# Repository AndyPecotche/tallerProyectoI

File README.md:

# Pasos 
1. Teniendo un workspace funcioal en eclipse, apuntando a un firmware_v3 ya funcionando, dirigirse a la carpeta donde se encuentra el mismo en el sistema.
1. Una vez en el directorio donde se encuentra el proyecto con un nombre como "firmware_v3-r1.3.0" o "firmware_v3" o "firmware_v3-master", eliminar o mover o renombrar esa carpeta a otro lado.
1. Clonar este repositorio
1. Renombrar el directorio del repositorio clonado con el mismo nombre del directorio del paso anterior (es importante que sea exactamente el mismo).
1. Al abrir eclipse en el workspace que se venia trabajando se deberia reconocer el nuevo proyecto con algunos cambios, pero aun funcionando los comandos de build y deploy.

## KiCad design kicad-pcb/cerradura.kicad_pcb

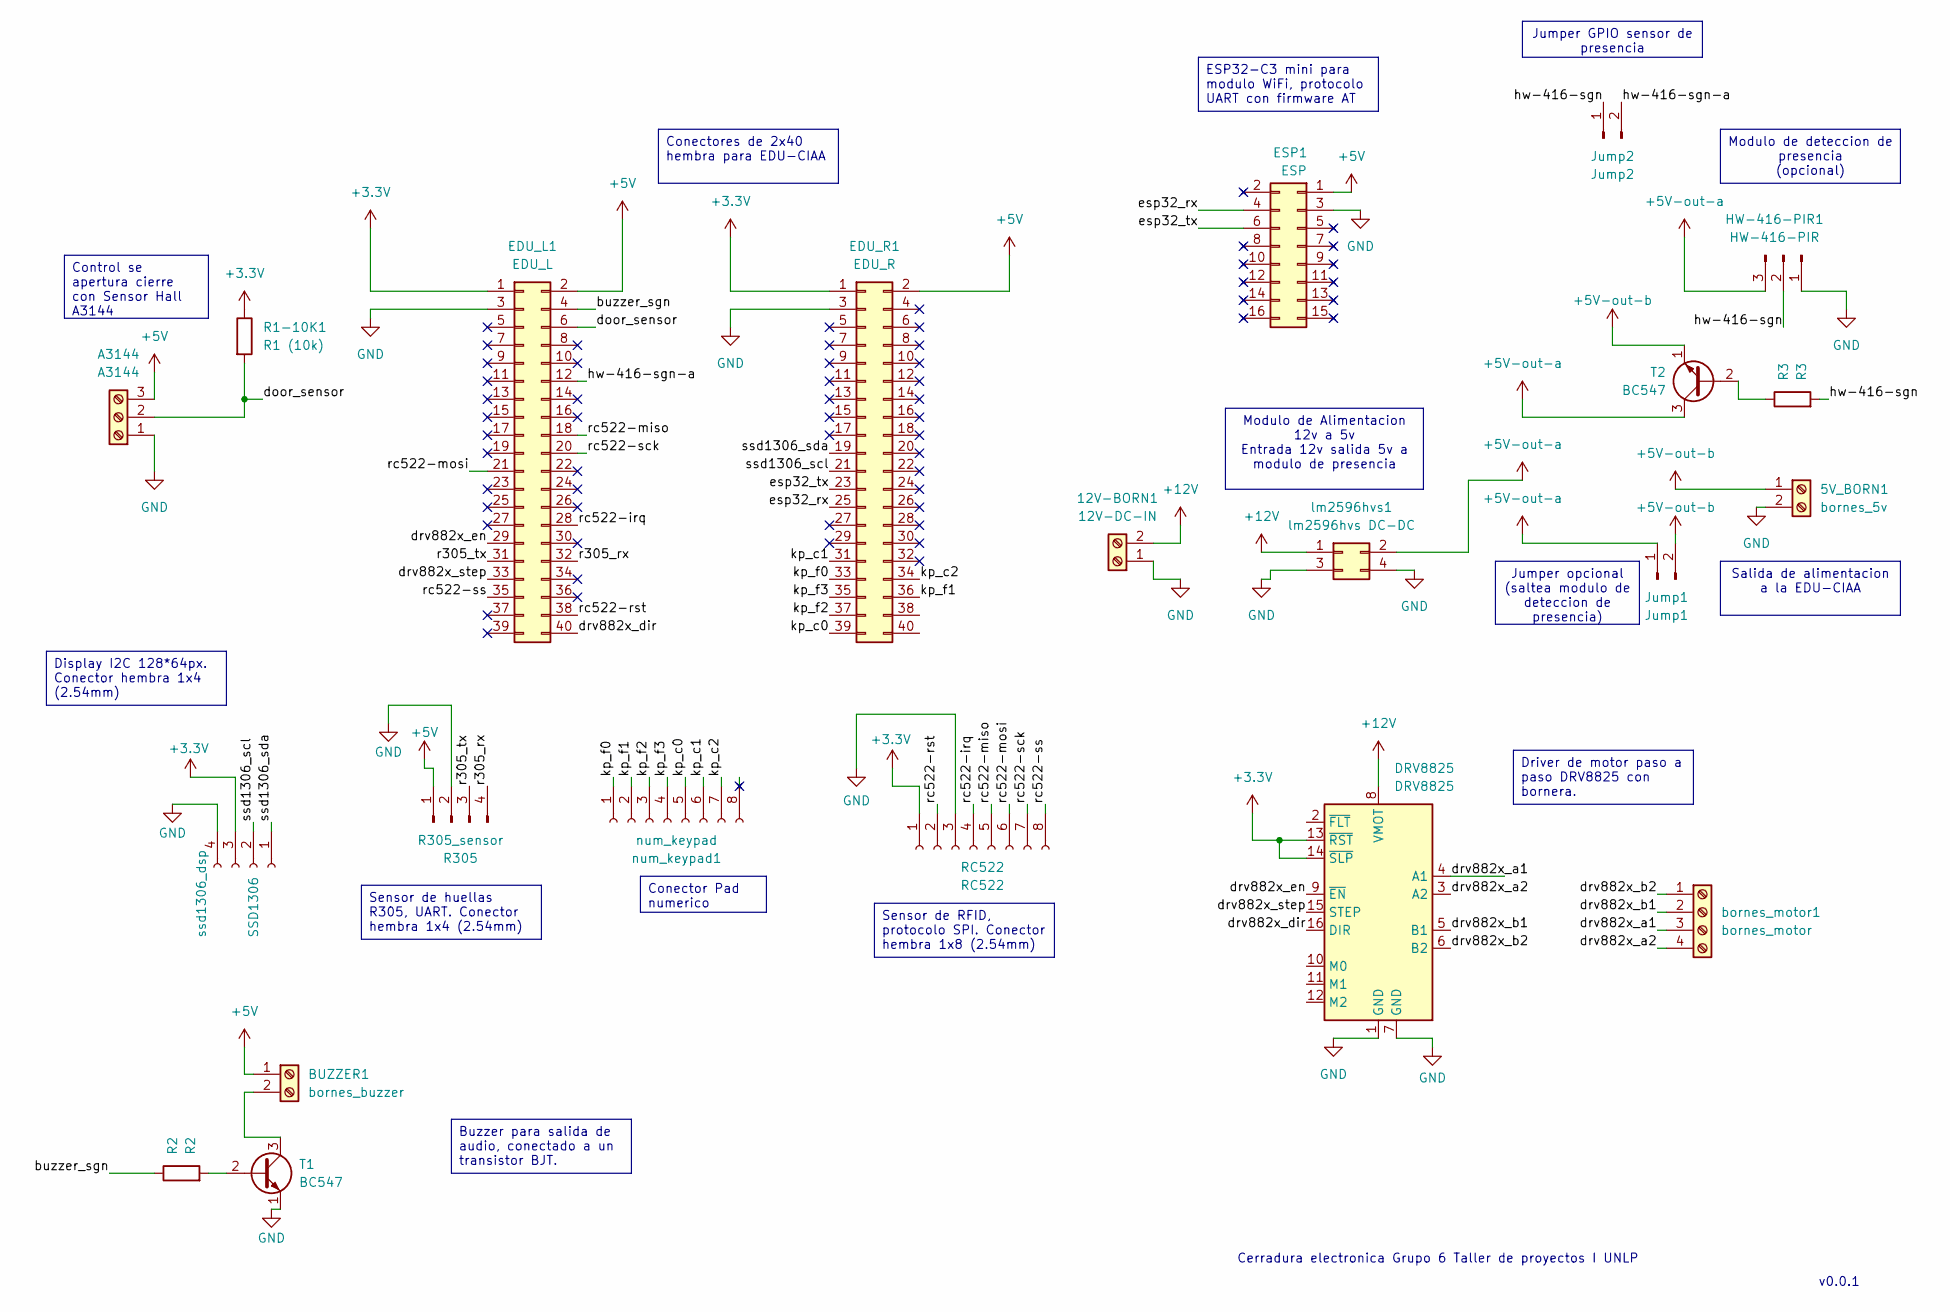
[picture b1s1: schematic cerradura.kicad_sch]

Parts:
5V_BORN1: bornes_5v; TerminalBlock_Altech_AK300-2_P5.00mm
12V-BORN1: 12V-DC-IN; TerminalBlock_Altech_AK300-2_P5.00mm
A3144: A3144; TerminalBlock_Altech_AK300-3_P5.00mm
BUZZER1: bornes_buzzer; TerminalBlock_Altech_AK300-2_P5.00mm
DRV8825: DRV8825; Pololu_Breakout-16_15.2x20.3mm
EDU_L1: EDU_L; IDC-Header_2x20_P2.54mm_Vertical
EDU_R1: EDU_R; IDC-Header_2x20_P2.54mm_Vertical
ESP1: ESP; PinSocket_2x08_P2.54mm_Vertical
HW-416-PIR1: HW-416-PIR; PinSocket_1x03_P2.54mm_Vertical
Jump1: Jump1; PinSocket_1x02_P2.54mm_Vertical
Jump2: Jump2; PinSocket_1x02_P2.54mm_Vertical
R1-10K1: R1 (10k); PinHeader_1x02_P1.00mm_Vertical
R2: R2; PinHeader_1x02_P1.00mm_Vertical
R3: R3; PinHeader_1x02_P1.00mm_Vertical
R305: R305_sensor; PinSocket_1x04_P2.54mm_Vertical
RC522: RC522; PinSocket_1x08_P2.54mm_Vertical
SSD1306: ssd1306_dsp; PinSocket_1x04_P2.54mm_Vertical
T1, T2: BC547; TO-92_Inline
bornes_motor1: bornes_motor; TerminalBlock_Altech_AK300-4_P5.00mm
lm2596hvs1: lm2596hvs DC-DC; PinSocket_2x02_P1.00mm_Vertical_SMD
num_keypad1: num_keypad; PinSocket_1x08_P2.54mm_Vertical

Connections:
+3.3V: DRV8825.13 (~RST), DRV8825.14 (~SLP), EDU_L1.1, EDU_R1.1, R1-10K1.1, RC522.1, SSD1306.3 (3v)
+5V: A3144.3, BUZZER1.1, EDU_L1.2, EDU_R1.2, ESP1.1 (5v), R305.1 (5v)
+5V-out-a: HW-416-PIR1.3, Jump1.1, T2.3 (C), lm2596hvs1.2 (out+)
+5V-out-b: 5V_BORN1.1, Jump1.2, T2.1 (E)
+12V: 12V-BORN1.2, DRV8825.8 (VMOT), lm2596hvs1.1 (in+)
/buzzer_sgn: EDU_L1.4, R2.1
/door_sensor: A3144.2, EDU_L1.6, R1-10K1.2
/drv882x_a1: DRV8825.4 (A1), bornes_motor1.3
/drv882x_a2: DRV8825.3 (A2), bornes_motor1.4
/drv882x_b1: DRV8825.5 (B1), bornes_motor1.2
/drv882x_b2: DRV8825.6 (B2), bornes_motor1.1
/drv882x_dir: DRV8825.16 (DIR), EDU_L1.40
/drv882x_en: DRV8825.9 (~EN), EDU_L1.29
/drv882x_step: DRV8825.15 (STEP), EDU_L1.33
/esp32_rx: EDU_R1.25, ESP1.4 (RX)
/esp32_tx: EDU_R1.23, ESP1.6 (TX)
/hw-416-sgn: HW-416-PIR1.2, Jump2.1, R3.2
/hw-416-sgn-a: EDU_L1.12, Jump2.2
/kp_c0: EDU_R1.39, num_keypad1.5 (C0)
/kp_c1: EDU_R1.31, num_keypad1.6 (C1)
/kp_c2: EDU_R1.34, num_keypad1.7 (C2)
/kp_f0: EDU_R1.33, num_keypad1.1 (F0)
/kp_f1: EDU_R1.36, num_keypad1.2 (F1)
/kp_f2: EDU_R1.37, num_keypad1.3 (F2)
/kp_f3: EDU_R1.35, num_keypad1.4 (F3)
/r305_rx: EDU_L1.32, R305.4 (RX)
/r305_tx: EDU_L1.31, R305.3 (TX)
/rc522-irq: EDU_L1.28, RC522.4
/rc522-miso: EDU_L1.18, RC522.5
/rc522-mosi: EDU_L1.21, RC522.6
/rc522-rst: EDU_L1.38, RC522.2
/rc522-sck: EDU_L1.20, RC522.7
/rc522-ss: EDU_L1.35, RC522.8
/ssd1306_scl: EDU_R1.21, SSD1306.2 (scl)
/ssd1306_sda: EDU_R1.19, SSD1306.1 (sda)
GND: 5V_BORN1.2, 12V-BORN1.1, A3144.1, DRV8825.1 (GND), DRV8825.7 (GND), EDU_L1.3, EDU_R1.3, ESP1.3 (G), HW-416-PIR1.1, R305.2 (GND), RC522.3, SSD1306.4 (gnd), T1.1 (E), lm2596hvs1.3 (in-), lm2596hvs1.4 (out-)
unnamed: BUZZER1.2, T1.3 (C)
unnamed: R2.2, T1.2 (B)
unnamed: R3.1, T2.2 (B)

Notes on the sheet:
v0.0.1
Cerradura electronica Grupo 6 Taller de proyectos I UNLP
Modulo de Alimentacion 12v a 5v Entrada 12v salida 5v a modulo de presencia
Driver de motor paso a paso DRV8825 con bornera.
Display I2C 128*64px. Conector hembra 1x4 (2.54mm)
Jumper opcional (saltea modulo de deteccion de presencia)
Salida de alimentacion a la EDU-CIAA
Modulo de deteccion de presencia (opcional)
Control se apertura cierre con Sensor Hall A3144
Conectores de 2x40 hembra para EDU-CIAA
Buzzer para salida de audio, conectado a un transistor BJT.
Jumper GPIO sensor de presencia
Conector Pad numerico
ESP32-C3 mini para modulo WiFi, protocolo UART con firmware AT
Sensor de huellas R305, UART. Conector hembra 1x4 (2.54mm)
Sensor de RFID, protocolo SPI. Conector hembra 1x8 (2.54mm)

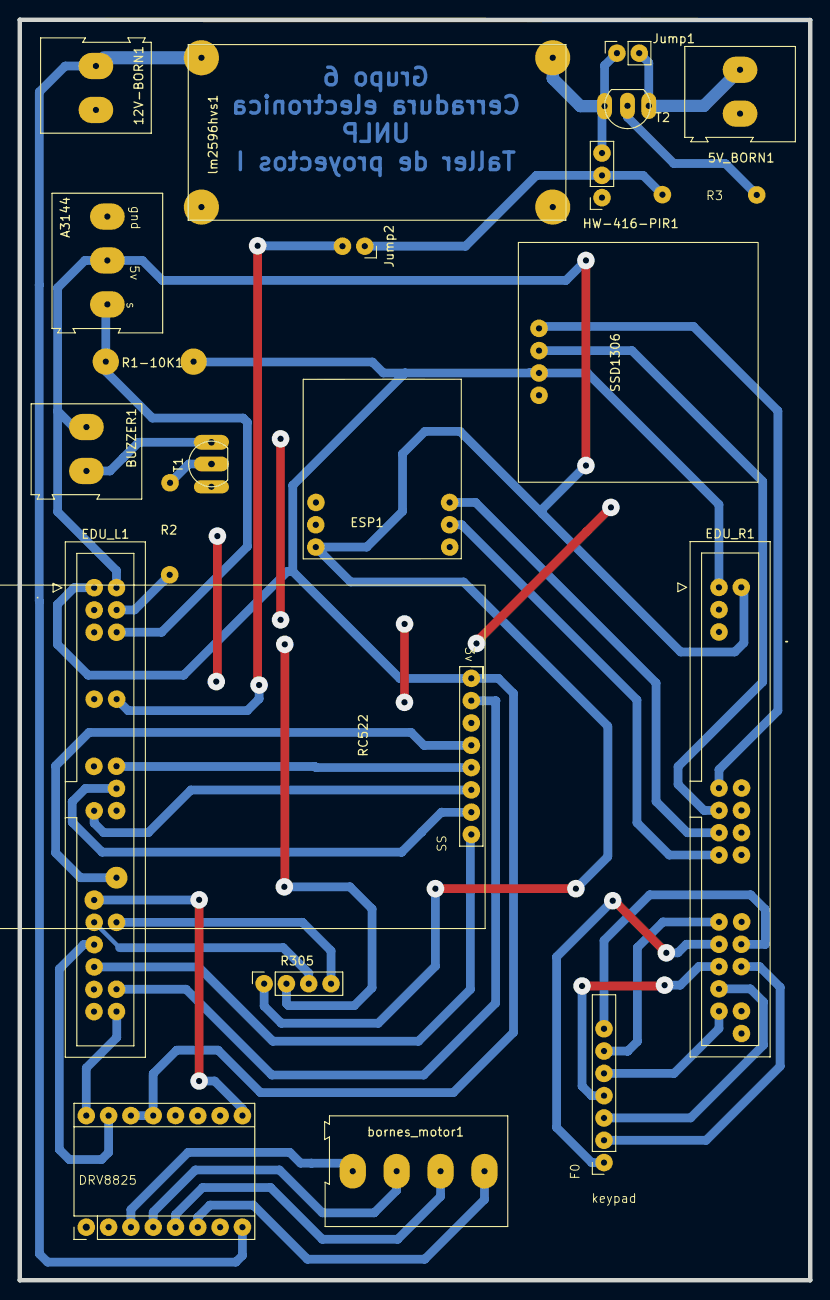
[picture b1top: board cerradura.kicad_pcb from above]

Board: 2 copper layers, 90.0 x 143.5 mm, 22 parts (0 on the bottom side), 39 nets.

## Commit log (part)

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2025-11-17 .vscode ignore
2025-11-19 Subir implementación inicial de stepperMotor.c
    Incluye funciones básicas para mover el motor y generar pulsos.
2025-11-19 Add files via upload
    Incluye prototipos de funciones y definiciones del driver del motor paso a paso.
2025-11-19 Add driver configuration in main function
2025-11-19 Add stepperMotor.h include to MEF.h
2025-11-19 Implement sensor-based closure in MEF.c
    Added sensor functionality to close the lock automatically when the sensor is triggered. Updated state transitions to include sensor checks and modified access control logic.
2025-11-19 Add comments to step_move function calls in MEF.c
2025-11-27 subimos proyecto andando en pc de valen
2025-11-27 eliminamos carpeta raiz
2025-11-27 estos archivos se deberian subir????
2025-11-28 cambio programa
2025-11-28 Proyecto sin carpeta raiz (#2)
    * subimos proyecto andando en pc de valen
    * eliminamos carpeta raiz
    * estos archivos se deberian subir????
    * cambio programa
    ---------
2025-11-28 Arreglo error nombre mef, por MEF
2025-11-29 funcionando motor y sensor cierre
2025-11-29 funcionando motor y sensor cierre (#3)
2025-11-29 Cambio codigo acceso menu
2025-11-30 ESP funcionando, y MEF mejorada
2025-11-30 Sleep funcionando correctamente
2025-11-30 Integracion WiFi provisioning desde MCU
2025-12-01 funcionando
2025-12-01 elimino checkeo baudrate
2025-12-01 Mejora enrroll
2025-12-01 Funcion abrir y cerrar motor
2025-12-01 recorte as608
2025-12-01 mas recortes
2025-12-01 cambios teclados no muy buenos
2025-12-01 ajustes tiempos sensor as
2025-12-01 Funciona bien pero solo guarda id 1
2025-12-01 sensores presencia y rfid exterons configurados
2025-12-01 mejoras deteccion enroll huella
2025-12-01 Mejoras enroll
2025-12-01 eliminacion codigo sin uso
2025-12-01 fix huella sin ID
2025-12-02 Creacion mef config
2025-12-02 limpieza codigo mef
2025-12-04 fix cantidad chars del ID huella leido del json
2025-12-11 fix sincronizacion inicial doble
2026-02-10 agrego cambios alan + RFID funcionando
2026-02-10 elimino cosas
2026-02-20 mejoras tiempo sync
2026-02-22 intentos huella limitados
2026-02-28 agrego server
2026-02-28 agrego workspace
2026-02-28 agrego pcb
